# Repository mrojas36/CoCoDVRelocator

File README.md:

# CoCoDV Relocator Board

This board allows AC's 8-bit Zone CoCoDV board to be placed into a Color Computer 1 Revision F board *without* cutting the center post.

Link to the AC's Youtube video
https://youtu.be/kyM9iXJTBaA

Here is a rendering of the board

And what the board looks like installed

## Bonus

I also designed a 3-D printed case for the remote control board for the CoCoDV.  Is it located in the CoCoDvCase folder.  It does not require any cutting of the case.  It just fits between the two case shells very securely.

You can see here how it just fits over the edge of the bottom case.

Here is the complete setup - AC's CoCoDV provides an incredibly sharp picture!

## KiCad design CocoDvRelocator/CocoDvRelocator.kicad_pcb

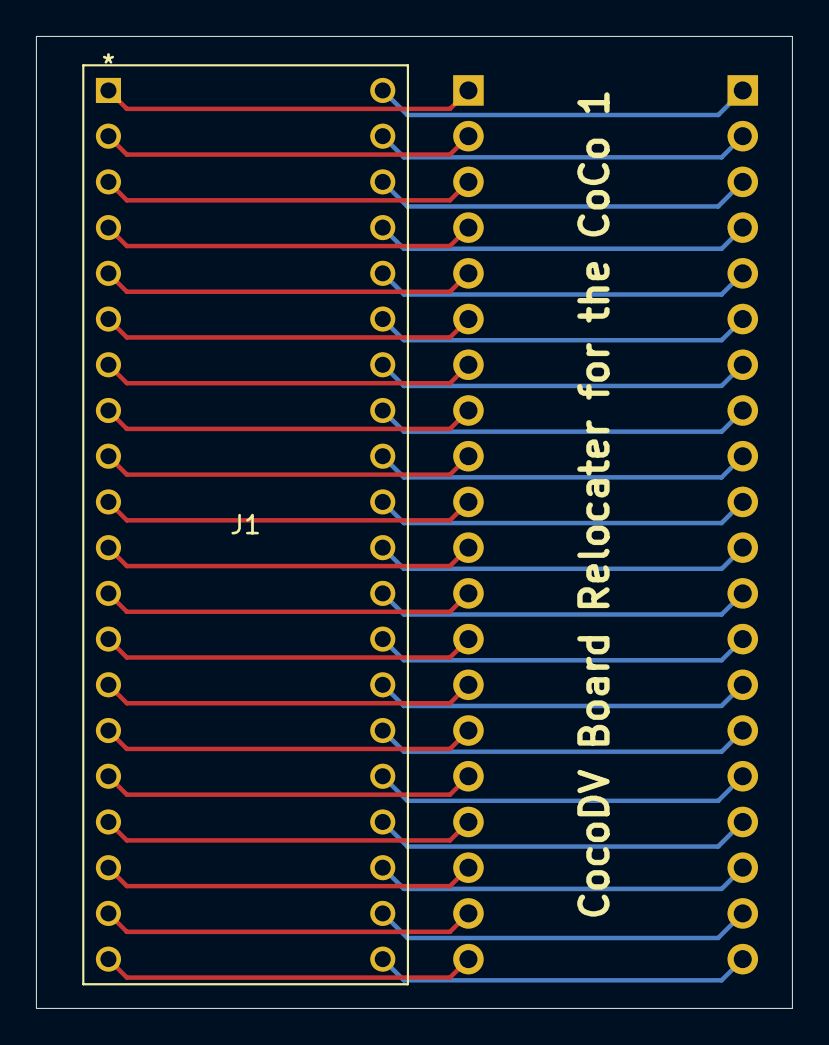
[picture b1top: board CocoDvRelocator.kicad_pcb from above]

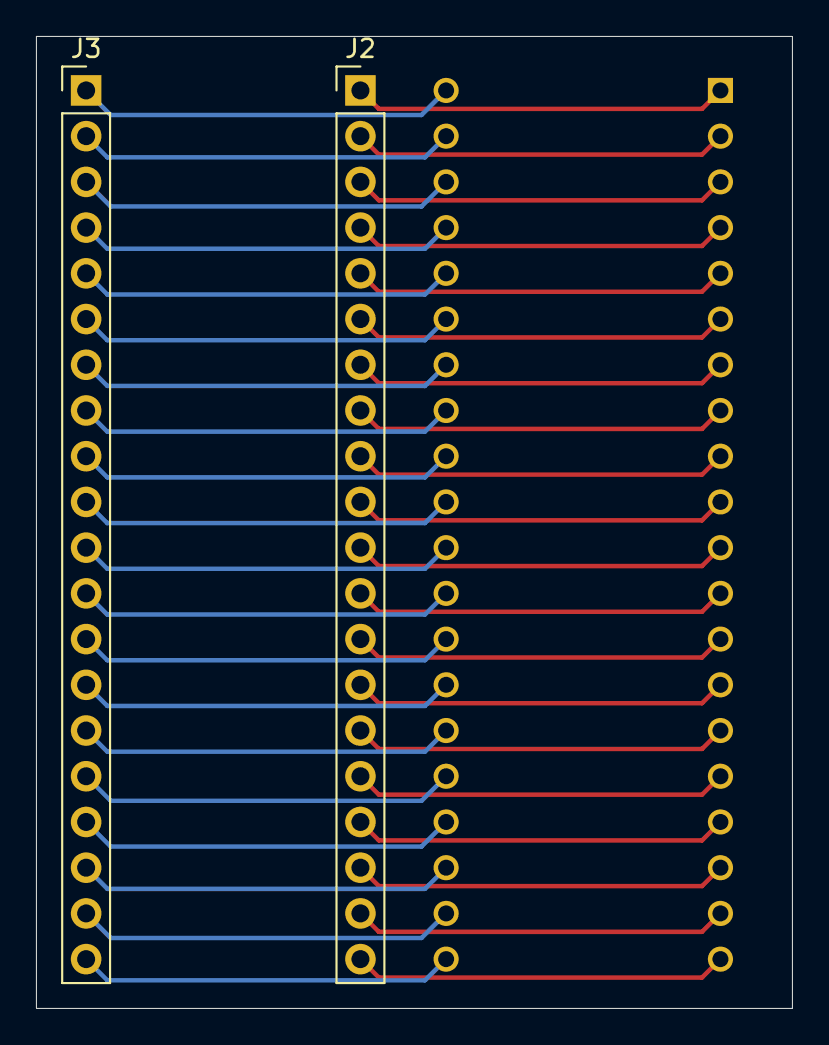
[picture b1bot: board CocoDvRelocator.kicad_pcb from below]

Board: 2 copper layers, 42.0 x 54.0 mm, 3 parts (2 on the bottom side), 40 nets.

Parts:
J1: CONN_3-1571586-2_TYCO; 3-1571586-2
J2, J3: Conn_01x20; PinHeader_1x20_P2.54mm_Vertical

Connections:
unnamed: J1.1, J2.1
unnamed: J1.2, J2.2
unnamed: J1.3, J2.3
unnamed: J1.4, J2.4
unnamed: J1.5, J2.5
unnamed: J1.6, J2.6
unnamed: J1.7, J2.7
unnamed: J1.8, J2.8
unnamed: J1.9, J2.9
unnamed: J1.10, J2.10
unnamed: J1.11, J2.11
unnamed: J1.12, J2.12
unnamed: J1.13, J2.13
unnamed: J1.14, J2.14
unnamed: J1.15, J2.15
unnamed: J1.16, J2.16
unnamed: J1.17, J2.17
unnamed: J1.18, J2.18
unnamed: J1.19, J2.19
unnamed: J1.20, J2.20
unnamed: J1.21, J3.20
unnamed: J1.22, J3.19
unnamed: J1.23, J3.18
unnamed: J1.24, J3.17
unnamed: J1.25, J3.16
unnamed: J1.26, J3.15
unnamed: J1.27, J3.14
unnamed: J1.28, J3.13
unnamed: J1.29, J3.12
unnamed: J1.30, J3.11
unnamed: J1.31, J3.10
unnamed: J1.32, J3.9
unnamed: J1.33, J3.8
unnamed: J1.34, J3.7
unnamed: J1.35, J3.6
unnamed: J1.36, J3.5
unnamed: J1.37, J3.4
unnamed: J1.38, J3.3
unnamed: J1.39, J3.2
unnamed: J1.40, J3.1

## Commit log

2023-02-16 Added pictures
2023-02-16 Update README.md
    Added the pictures
2023-02-16 Update README.md
    Spacing adjustments

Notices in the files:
parts and their libraries:
Copyright 2021 Accelerated Designs. All rights reserved.
